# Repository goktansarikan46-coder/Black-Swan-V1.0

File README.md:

# Black-Swan V1.0 | Wireless Biomedical & Seismic Sensor Node

Black-Swan V1.0, saha verilerini işlemek ve uzun menzilli kablosuz ağlar üzerinden aktarmak için geliştirdigim, düşük güç tüketimli bir "Edge" sensör düğümüdür. Proje kapsamında, biyomedikal sinyal işleme (AFE) yeteneklerini savunma sanayii standartlarında RF güvenilirliği ile tek bir PCB üzerinde birlestirmeyi hedefledim.

## Teknik Özellikler

* **Mikrodenetleyici (MCU):** STM32L431RCT6 (Ultra-Low Power ARM Cortex-M4).
* **Kablosuz Haberleşme (RF):** SX1278 LoRa modülü entegrasyonu ve 50 $\Omega$ empedans uyumlu SMA anten çıkışı.
* **Analog Ön Uç (AFE):** EKG, EMG veya sismik veriler için optimize edilmiş 3-Op-Amp enstrümantasyon amplifikatörü.
* **Atalet Sensörü (IMU):** 6-eksenli hareket takibi için entegre MPU-6050.
* **Güç Yönetimi:** USB-C üzerinden besleme hattı ve gürültü regülasyonu için molded güç indüktörü (L1).

## Proje Yapısı

* `/Hardware`: KiCad şematik (.kicad_sch) ve PCB (.kicad_pcb) tasarım dosyaları.
* `/Hardware/BOM`: Malzeme listesi ve bileşen detayları.
* `/Docs`: Tasarım raporları ve 3D render görselleri.

## Tasarım Kararları

RF bütünlüğü ve analog sinyal kalitesini korumak adına genel amaçlı genişleme portlarını V2.0 sürümüne planladım.

---
**Hazırlayan:** Göktan Sarıkan (Yıldız Teknik Üniversitesi)
**Tarih:** Mart 2026

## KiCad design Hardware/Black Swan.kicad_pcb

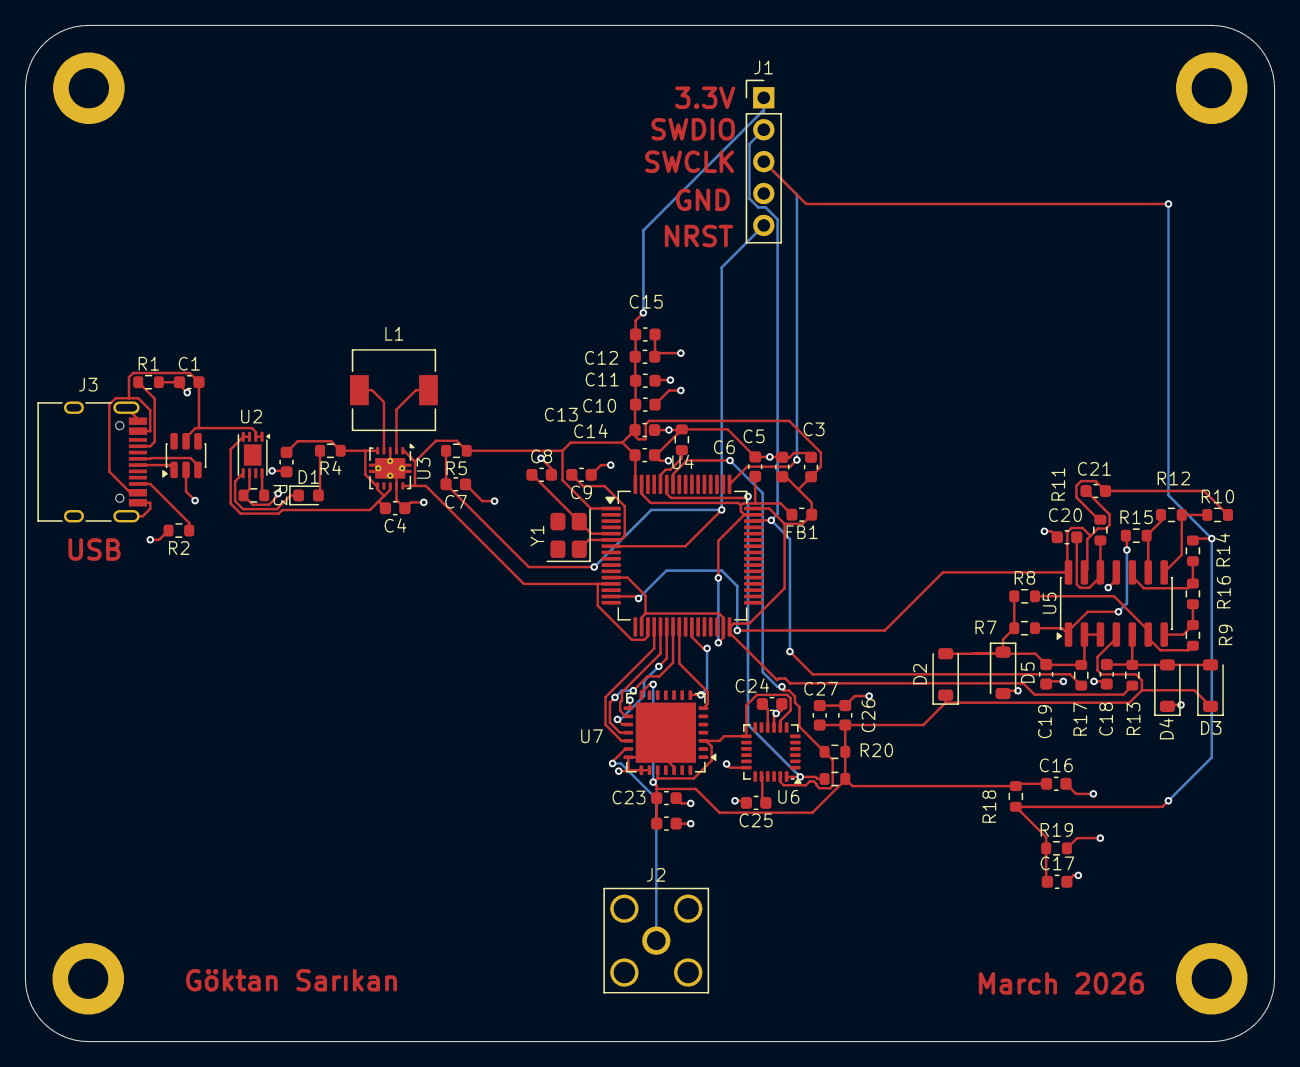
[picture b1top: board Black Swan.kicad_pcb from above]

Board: 2 copper layers, 99.4 x 80.9 mm, 66 parts (0 on the bottom side), 43 nets.

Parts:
C1, C2, C4, C23, C27: 10uF; C_0603_1608Metric
C3: 22uF; C_0603_1608Metric
C5, C6, C7, C10, C11, C12, C13, C14, C15, C16, C17, C18, C19, C22, C26: 100nF; C_0603_1608Metric
C8, C9: 20pF; C_0603_1608Metric
C20, C21, C24: 10nF; C_0603_1608Metric
C25: 2.2nF; C_0603_1608Metric
D1: LED; D_0603_1608Metric
D2, D3, D4, D5: 1N4148; D_SOD-123
FB1: 120R; L_0603_1608Metric
J1: Conn_01x05_Pin; PinHeader_1x05_P2.54mm_Vertical
J2: Conn_Coaxial_Small; SMA_Amphenol_132203-12_Horizontal
J3: USB_C_Receptacle_USB2.0_14P; USB_C_Receptacle_HRO_TYPE-C-31-M-12
L1: 2.2uH; L_6.3x6.3_H3
R1, R2: 5.2k; R_0603_1608Metric
R3, R4: 2k; R_0603_1608Metric
R5, R6, R12, R14, R15, R16, R18, R19: 10k; R_0603_1608Metric
R7, R9: 25k; R_0603_1608Metric
R8: 5.5k; R_0603_1608Metric
R10, R11: 16k; R_0603_1608Metric
R13, R17: 200k; R_0603_1608Metric
R20, R21: 4.7k; R_0603_1608Metric
U1: USBLC6-2SC6; SOT-23-6
U2: MCP73831-2-MC; DFN-8-1EP_3x2mm_P0.5mm_EP1.7x1.4mm
U3: TPS63001; Texas_DRC0010J_ThermalVias
U4: STM32L431RCTx; LQFP-64_10x10mm_P0.5mm
U5: MCP6004; SOIC-14_3.9x8.7mm_P1.27mm
U6: MPU-6050; InvenSense_QFN-24_4x4mm_P0.5mm
U7: SX1278; QFN-28-1EP_6x6mm_P0.65mm_EP4.8x4.8mm
Y1: 8MHz; Crystal_SMD_3225-4Pin_3.2x2.5mm

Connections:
+3.3VA: C16.1, C22.1, C23.1, C26.1, C27.1, D2.1 (K), D3.1 (K), R18.1, R20.1, R21.2, U5.4 (V+), U6.8 (VLOGIC), U6.13 (VDD), U7.3 (VBAT_ANA), U7.14 (VBAT_DIG), U7.24 (VBAT_RF)
/3.3V: C3.1, C5.1, C10.2, C11.2, C12.2, C13.2, C14.2, C15.2, FB1.1, J1.1, R5.1, R13.1, U3.1 (VOUT), U3.10 (FB), U4.1 (VBAT), U4.13 (VDDA), U4.19 (VDD), U4.32 (VDD), U4.48 (VDD), U4.64 (VDD)
/3.3VA: C6.1, FB1.2, U4.12 (VSSA), U4.18 (VSS), U4.31 (VSS), U4.47 (VSS), U4.63 (VSS)
/ANALOG_FRONT_END/ECG_OUT: C21.2, U4.15 (PA1), U5.13 (-), U5.14
/ANALOG_FRONT_END/IN_RA: J1.2, R17.1, U4.46 (PA13)
/ANALOG_FRONT_END/IN_RL: C17.1, J1.3, R14.1, R18.2, R19.1, U4.49 (PA14)
/RF Sensors/I2C1_SCL: R20.2, U4.58 (PB6), U6.23 (SCL)
/RF Sensors/I2C1_SDA: R21.1, U4.59 (PB7), U6.24 (SDA)
/RF Sensors/LORA_CS: U4.20 (PA4), U7.19 (NSS)
/RF Sensors/LORA_DIO0: U4.26 (PB0), U7.8 (DIO0)
/RF Sensors/LORA_RST: U4.24 (PC4), U7.7 (~RESET)
/RF Sensors/SPI1_MISO: U4.22 (PA6), U7.17 (MISO)
/RF Sensors/SPI1_MOSI: U4.23 (PA7), U7.18 (MOSI)
/RF Sensors/SPI1_SCK: U4.21 (PA5), U7.16 (SCK)
/VBat: C2.2, C4.2, R4.1, U2.3 (V_{BAT}), U2.4 (V_{BAT}), U3.5 (VIN), U3.6 (EN), U3.8 (VINA)
/VBus: C1.2, J3.A4 (VBUS), J3.A9 (VBUS), J3.B4 (VBUS), J3.B9 (VBUS), U1.5 (VBUS), U2.1 (V_{DD}), U2.2 (V_{DD})
GND: C1.1, C2.1, C3.2, C4.1, C5.2, C6.2, C7.1, C8.2, C9.1, C10.1, C11.1, C12.1, C13.1, C14.1, C15.1, C16.2, C17.2, C18.2, C19.2, C20.2, C22.2, C23.2, C24.1, C25.2, C26.2, C27.2, D4.1 (K), D5.2 (A), J1.4, J2.2 (Ext), J3.A1 (GND), J3.A12 (GND), J3.B1 (GND), J3.B12 (GND), J3.S1 (SHIELD), R1.2, R2.2, R3.1, R6.2, R19.2, U1.2 (GND), U2.6 (V_{SS}), U3.3 (PGND), U3.9 (GND), U3.11 (PGND), U5.11 (V-), U6.9 (AD0), U6.18 (GND), U7.15 (GND), U7.21 (GND), U7.22 (GND), U7.23 (GND), U7.26 (GND), U7.29 (GND)
unnamed: C21.1, R10.2, R11.1
unnamed: D1.2 (A), R4.2
unnamed: D1.1 (K), U2.5 (STAT)
unnamed: C19.1, D2.2 (A), D5.1 (K), R7.2, R8.1, R17.2, U5.2 (-), U5.3 (+)
unnamed: C18.1, D3.2 (A), D4.2 (A), R13.2, U5.5 (+)
unnamed: C7.2, J1.5, R5.2, U4.7 (NRST)
unnamed: J2.1 (In), U7.20 (RXTX/RF_MOD)
unnamed: J3.A5 (CC1), R1.1
unnamed: J3.B5 (CC2), R2.1
unnamed: J3.A6 (D+), U1.3 (I/O2)
unnamed: J3.A7 (D-), U1.1 (I/O1)
unnamed: R10.1, R12.2, U5.8
unnamed: R7.1, R15.1, U5.1
unnamed: R9.2, R16.1, U5.7
unnamed: R3.2, U2.8 (PROG)
unnamed: L1.1, U3.4 (L1)
unnamed: L1.2, U3.2 (L2)
unnamed: C8.1, U4.5 (PH0), Y1.2
unnamed: C9.2, U4.6 (PH1), Y1.1
unnamed: R6.1, U4.60 (PH3)
unnamed: R8.2, R9.1, U5.6 (-)
unnamed: R14.2, R16.2, U5.10 (+)
unnamed: R12.1, R15.2, U5.9 (-)
unnamed: C20.1, R11.2, U5.12 (+)
unnamed: C25.1, U6.20 (CPOUT)
unnamed: C24.2, U6.10 (REGOUT)

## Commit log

2026-03-07 Fix typo in README.md
    Corrected a typo in the project description.
2026-03-07 Fix typo in Black-Swan project description
    Corrected a typo in the project description.
